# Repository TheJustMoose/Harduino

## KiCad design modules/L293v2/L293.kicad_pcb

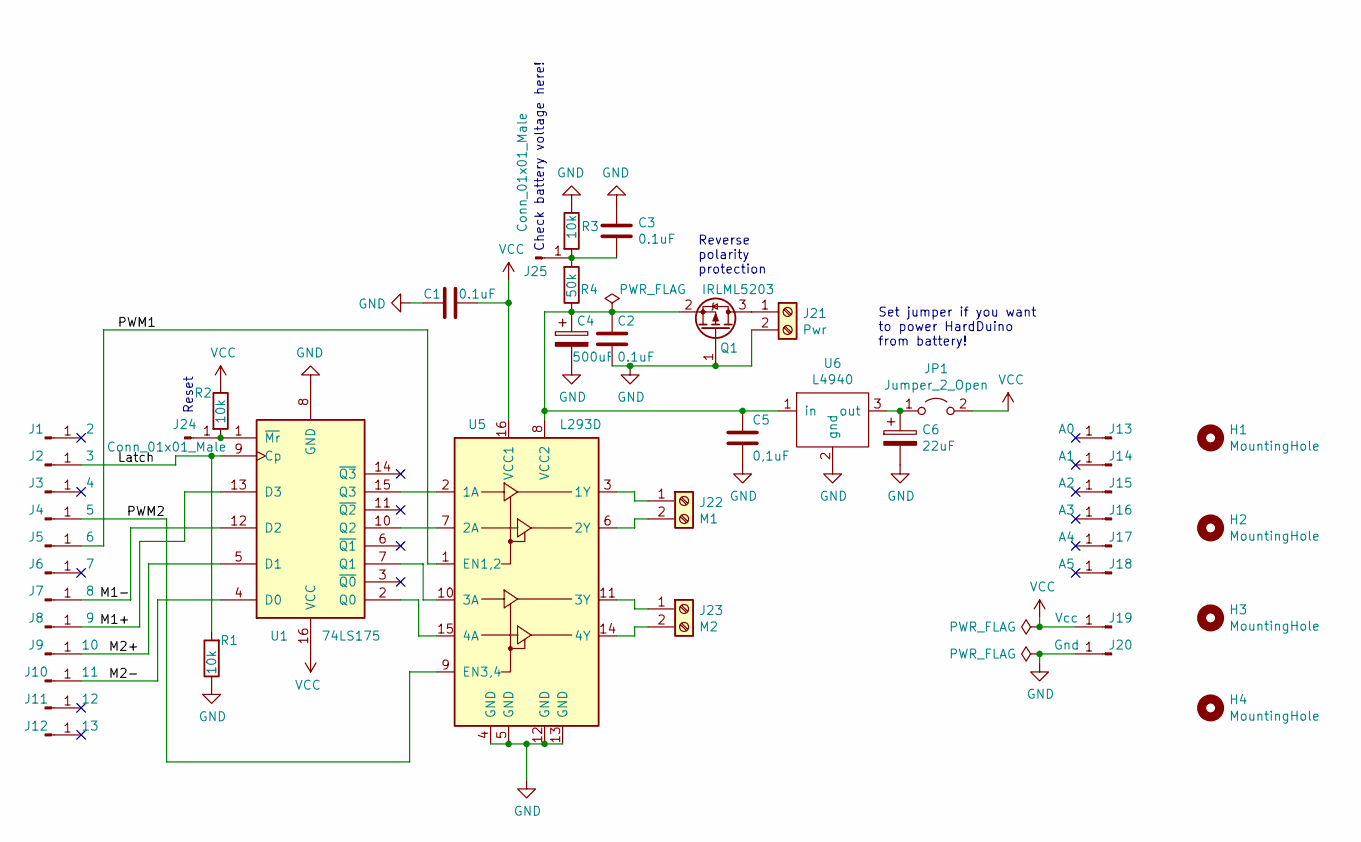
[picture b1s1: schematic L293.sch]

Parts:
C1, C2, C3: 0.1uF; C_0805_2012Metric_Pad1.15x1.40mm_HandSolder
C4: 500uF; CP_Radial_D8.0mm_P3.50mm
C5: 0,1uF; C_0805_2012Metric_Pad1.15x1.40mm_HandSolder
C6: 22uF; CP_Radial_D5.0mm_P2.50mm
H1, H2, H3, H4: MountingHole; MountingHole_3.2mm_M3
J1: 2; PinHeader_1x01_P2.54mm_Vertical
J2: 3; PinHeader_1x01_P2.54mm_Vertical
J3: 4; PinHeader_1x01_P2.54mm_Vertical
J4: 5; PinHeader_1x01_P2.54mm_Vertical
J5: 6; PinHeader_1x01_P2.54mm_Vertical
J6: 7; PinHeader_1x01_P2.54mm_Vertical
J7: 8; PinHeader_1x01_P2.54mm_Vertical
J8: 9; PinHeader_1x01_P2.54mm_Vertical
J9: 10; PinHeader_1x01_P2.54mm_Vertical
J10: 11; PinHeader_1x01_P2.54mm_Vertical
J11: 12; PinHeader_1x01_P2.54mm_Vertical
J12: 13; PinHeader_1x01_P2.54mm_Vertical
J13: A0; PinHeader_1x01_P2.54mm_Vertical
J14: A1; PinHeader_1x01_P2.54mm_Vertical
J15: A2; PinHeader_1x01_P2.54mm_Vertical
J16: A3; PinHeader_1x01_P2.54mm_Vertical
J17: A4; PinHeader_1x01_P2.54mm_Vertical
J18: A5; PinHeader_1x01_P2.54mm_Vertical
J19: Vcc; PinHeader_1x01_P2.54mm_Vertical
J20: Gnd; PinHeader_1x01_P2.54mm_Vertical
J21: Pwr; TerminalBlock_bornier-2_P5.08mm
J22: M1; TerminalBlock_bornier-2_P5.08mm
J23: M2; TerminalBlock_bornier-2_P5.08mm
J24, J25: Conn_01x01_Male; PinHeader_1x01_P2.54mm_Vertical
JP1: Jumper_2_Open; PinHeader_1x02_P2.54mm_Vertical
Q1: IRLML5203; SOT-23
R1, R2, R3: 10k; R_0805_2012Metric_Pad1.15x1.40mm_HandSolder
R4: 50k; R_0805_2012Metric_Pad1.15x1.40mm_HandSolder
U1: 74LS175; SOIC-16_3.9x9.9mm_P1.27mm
U5: L293D; DIP-16_W7.62mm
U6: L4940; TO-220-3_Horizontal_TabDown

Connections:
/Latch: J2.1, R1.2, U1.9 (Cp)
/M1+: J8.1, U1.13 (D3)
/M1-: J7.1, U1.12 (D2)
/M2+: J9.1, U1.5 (D1)
/M2-: J10.1, U1.4 (D0)
/PWM1: J5.1, U5.1 (EN1,2)
/PWM2: J4.1, U5.9 (EN3,4)
GND: C1.2, C2.1, C3.1, C4.2, C5.2, C6.2, J20.1, J21.2, Q1.1 (G), R1.1, R3.1, U1.8 (GND), U5.4 (GND), U5.5 (GND), U5.12 (GND), U5.13 (GND), U6.2 (gnd)
unnamed: C2.2, C4.1, C5.1, Q1.2 (S), R4.1, U5.8 (VCC2), U6.1 (in)
unnamed: C3.2, J25.1, R3.2, R4.2
unnamed: C6.1, JP1.1 (A), U6.3 (out)
unnamed: J21.1, Q1.3 (D)
unnamed: J22.1, U5.3 (1Y)
unnamed: J22.2, U5.6 (2Y)
unnamed: J23.1, U5.11 (3Y)
unnamed: J23.2, U5.14 (4Y)
unnamed: J24.1, R2.2, U1.1 (~Mr)
unnamed: U1.2 (Q0), U5.15 (4A)
unnamed: U1.7 (Q1), U5.10 (3A)
unnamed: U1.10 (Q2), U5.7 (2A)
unnamed: U1.15 (Q3), U5.2 (1A)
VCC: C1.1, J19.1, JP1.2 (B), R2.1, U1.16 (VCC), U5.16 (VCC1)

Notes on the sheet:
Set jumper if you want to power HardDuino from battery!
Check battery voltage here!
Reset
Reverse polarity protection

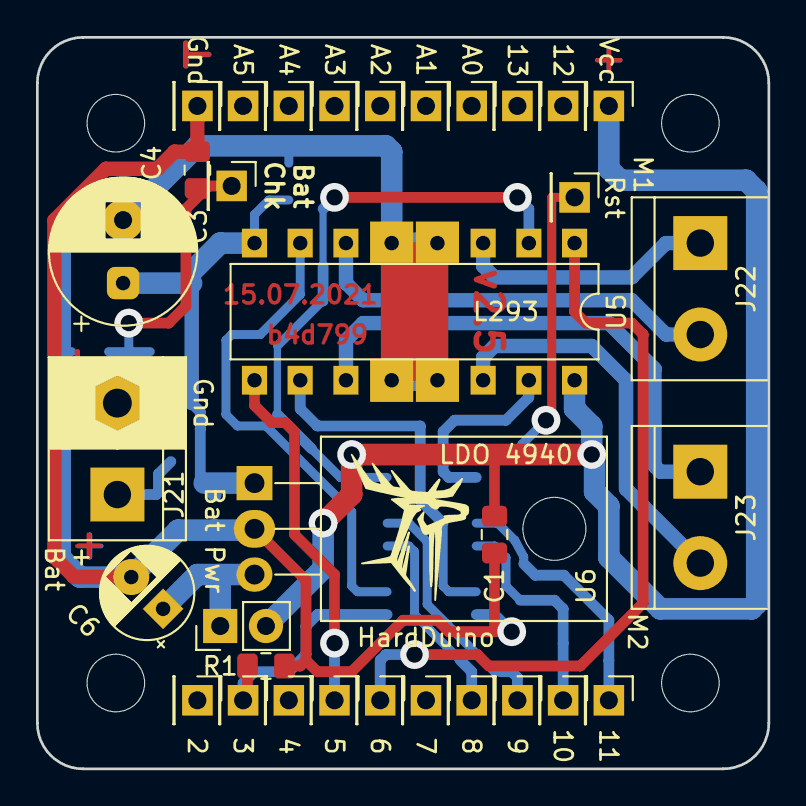
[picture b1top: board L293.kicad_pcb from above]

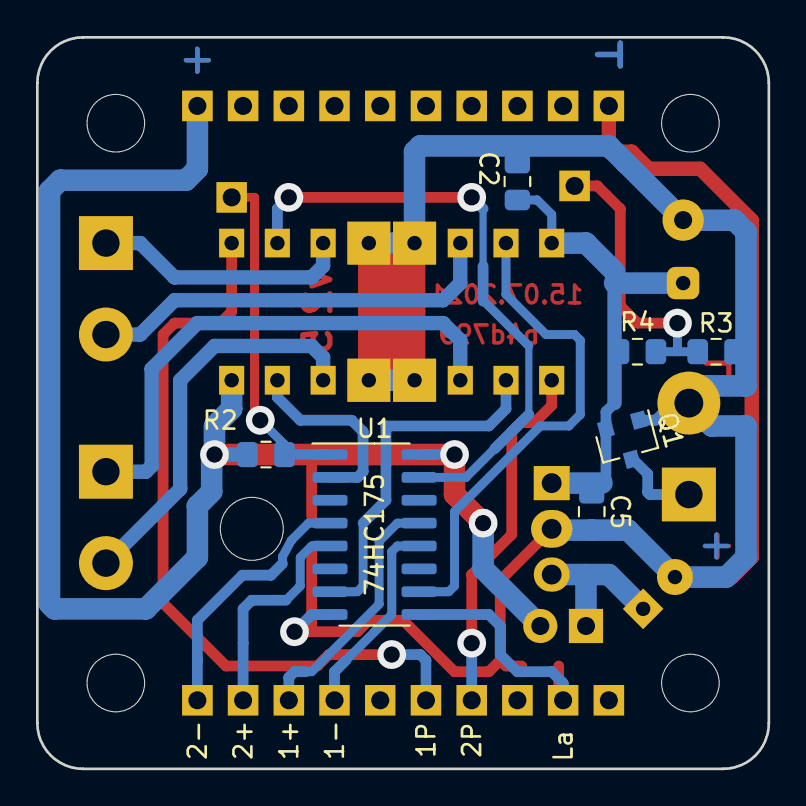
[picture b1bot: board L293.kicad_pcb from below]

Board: 2 copper layers, 40.6 x 40.6 mm, 44 parts (7 on the bottom side), 22 nets.

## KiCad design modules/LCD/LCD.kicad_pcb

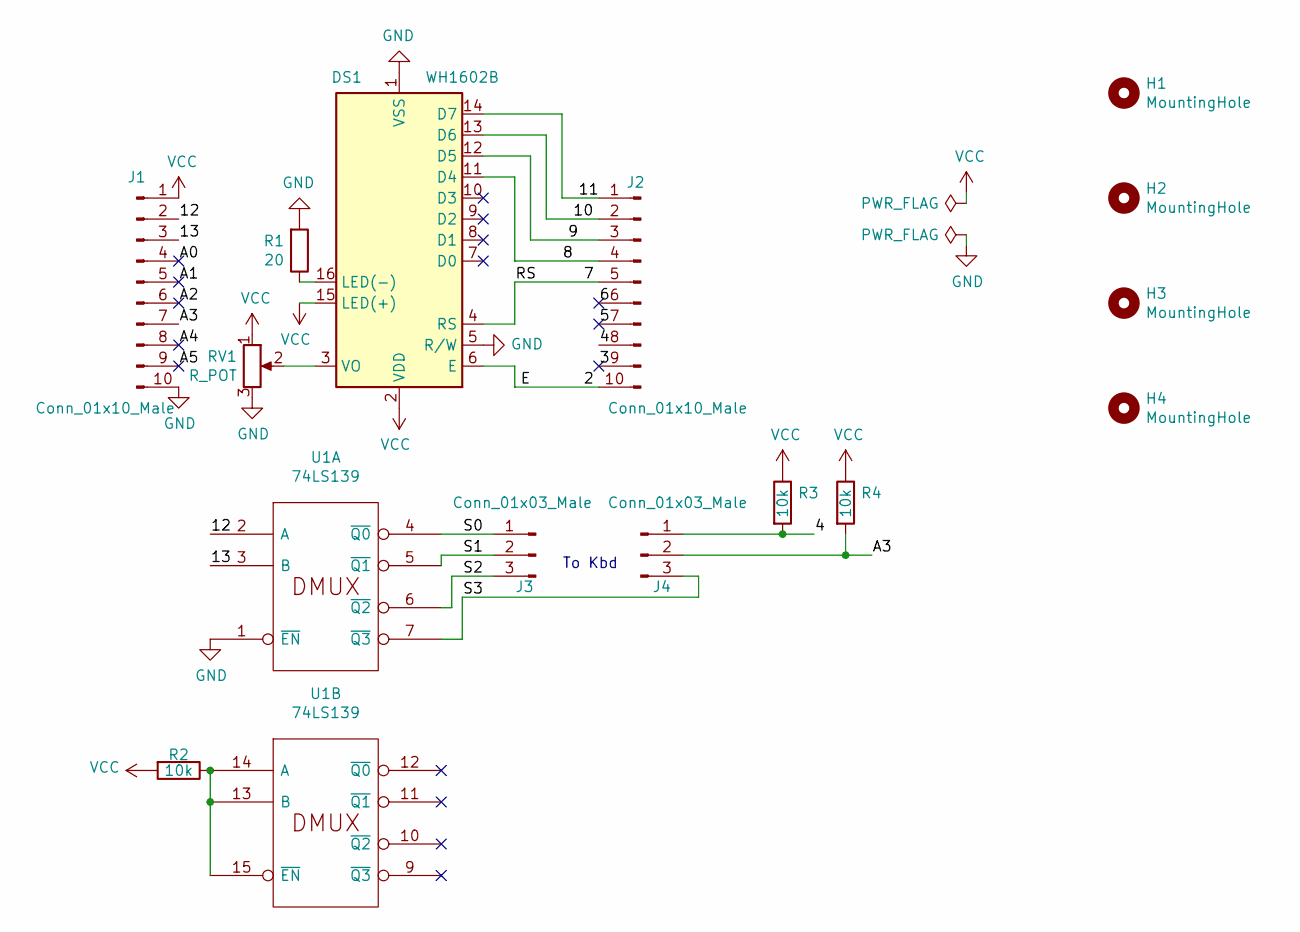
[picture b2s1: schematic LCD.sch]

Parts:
DS1: WH1602B; WH1602-2-holes
H1, H2, H3, H4: MountingHole; MountingHole_3.2mm_M3
J1, J2: Conn_01x10_Male; PinHeader_1x10_P2.54mm_Vertical
J3, J4: Conn_01x03_Male; PinHeader_1x03_P2.54mm_Horizontal
R1: 20; R_0805_2012Metric_Pad1.20x1.40mm_HandSolder
R2, R3, R4: 10k; R_0805_2012Metric_Pad1.20x1.40mm_HandSolder
RV1: R_POT; pot-5x5
U1: 74LS139; SOIC-16_3.9x9.9mm_P1.27mm

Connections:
/2: DS1.6 (E), J2.10
/3: J2.9
/4: J2.8, J4.1, R3.2
/5: J2.7
/6: J2.6
/7: DS1.4 (RS), J2.5
/8: DS1.11 (D4), J2.4
/9: DS1.12 (D5), J2.3
/10: DS1.13 (D6), J2.2
/11: DS1.14 (D7), J2.1
/12: J1.2, U1.2 (A)
/13: J1.3, U1.3 (B)
/A0: J1.4
/A1: J1.5
/A2: J1.6
/A3: J1.7, J4.2, R4.2
/A4: J1.8
/A5: J1.9
/S0: J3.1, U1.4 (~Q0)
/S1: J3.2, U1.5 (~Q1)
/S2: J3.3, U1.6 (~Q2)
/S3: J4.3, U1.7 (~Q3)
GND: DS1.1 (VSS), DS1.5 (R/W), J1.10, R1.2, RV1.3, U1.1 (~EN), U1.8 (GND)
unnamed: DS1.3 (VO), RV1.2
unnamed: DS1.16 (LED(-)), R1.1
unnamed: R2.1, U1.13 (B), U1.14 (A), U1.15 (~EN)
VCC: DS1.2 (VDD), DS1.15 (LED(+)), J1.1, R2.2, R3.1, R4.1, RV1.1, U1.16 (VCC)

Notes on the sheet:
To Kbd

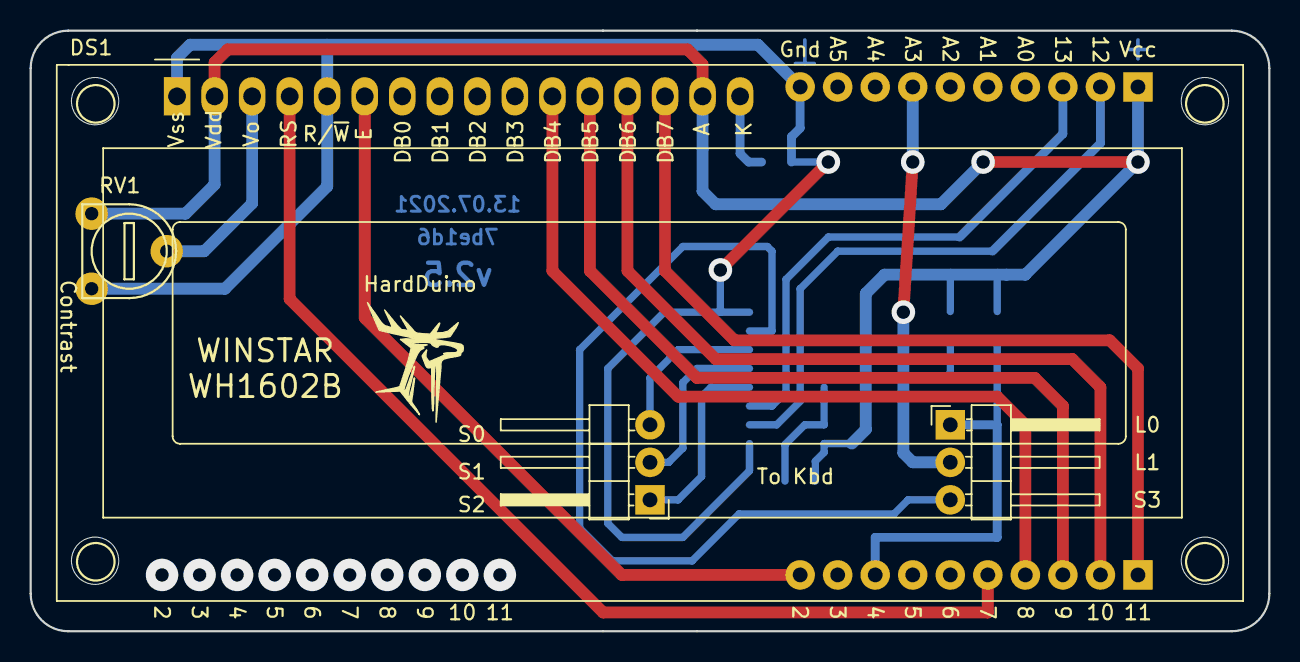
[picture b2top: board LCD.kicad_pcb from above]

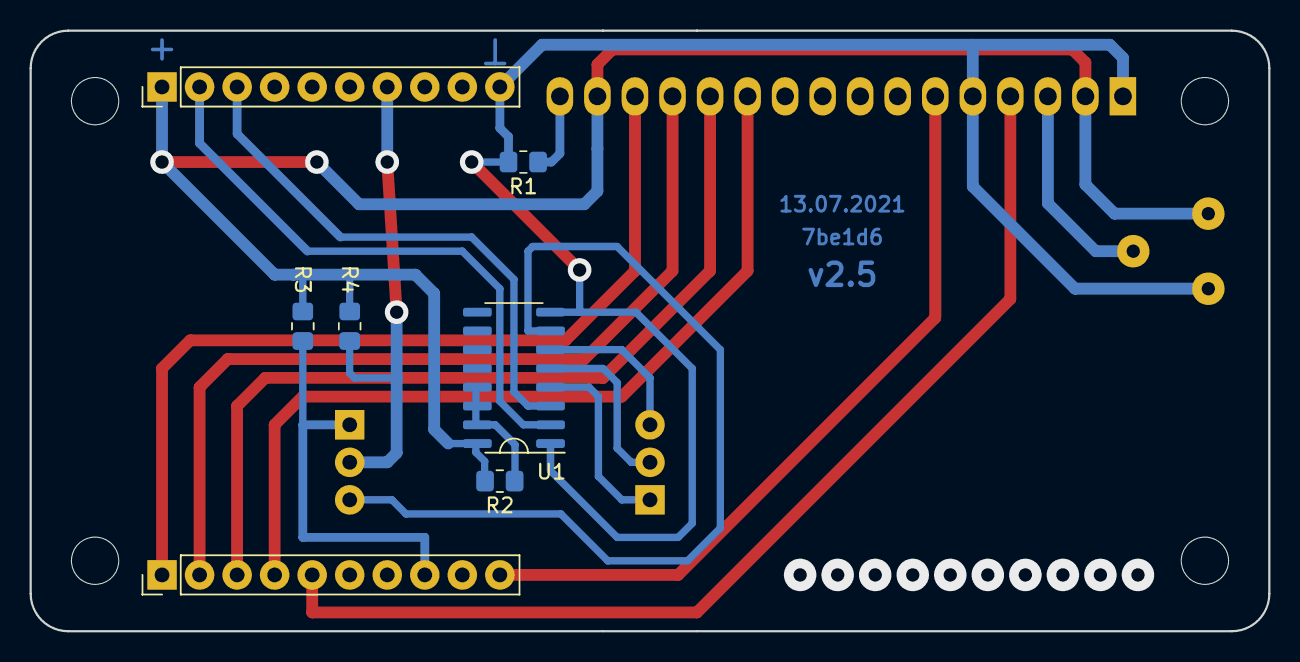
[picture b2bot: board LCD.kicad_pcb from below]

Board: 2 copper layers, 83.8 x 40.6 mm, 15 parts (7 on the bottom side), 19 nets.

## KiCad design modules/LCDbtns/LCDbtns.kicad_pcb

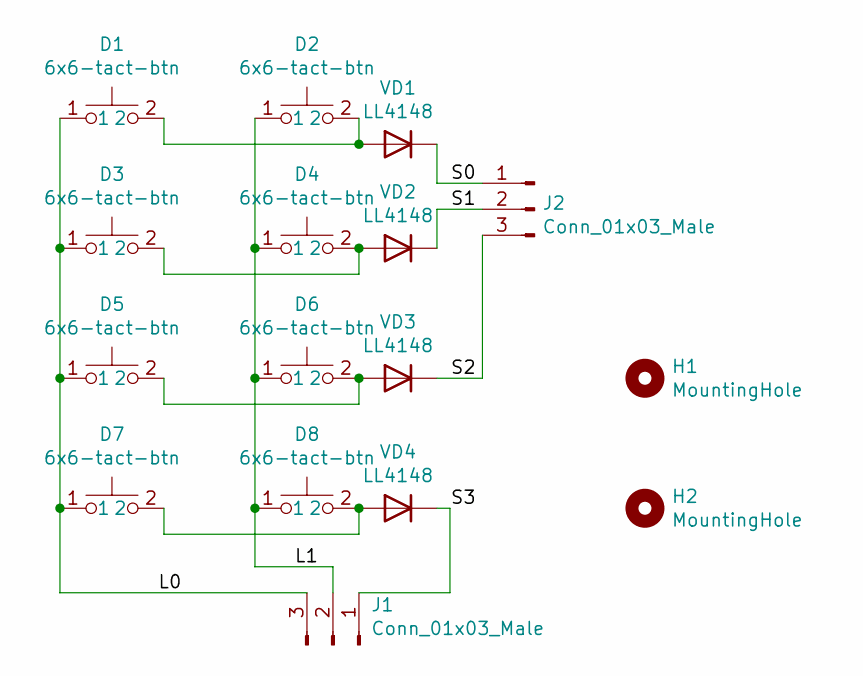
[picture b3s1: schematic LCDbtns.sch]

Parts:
D1, D2, D3, D4, D5, D6, D7, D8: 6x6-tact-btn
H1, H2: MountingHole; MountingHole_3.2mm_M3
J1, J2: Conn_01x03_Male; PinHeader_1x03_P2.54mm_Vertical
VD1, VD2, VD3, VD4: LL4148; D_MiniMELF

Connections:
/L0: D1.1, D3.1, D5.1, D7.1, J1.3
/L1: D2.1, D4.1, D6.1, D8.1, J1.2
/S0: J2.1, VD1.1 (K)
/S1: J2.2, VD2.1 (K)
/S2: J2.3, VD3.1 (K)
/S3: J1.1, VD4.1 (K)
unnamed: D1.2, D2.2, VD1.2 (A)
unnamed: D3.2, D4.2, VD2.2 (A)
unnamed: D5.2, D6.2, VD3.2 (A)
unnamed: D7.2, D8.2, VD4.2 (A)

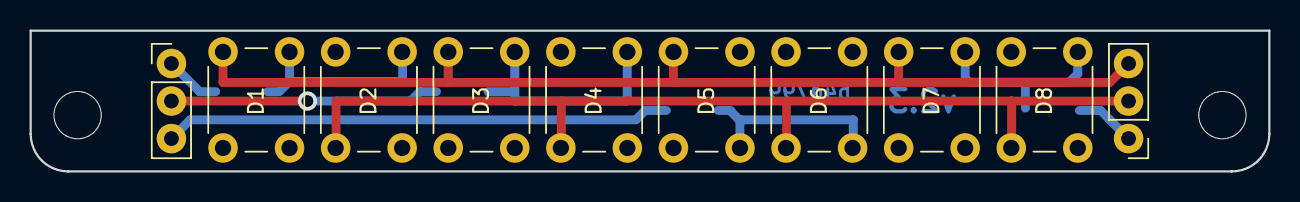
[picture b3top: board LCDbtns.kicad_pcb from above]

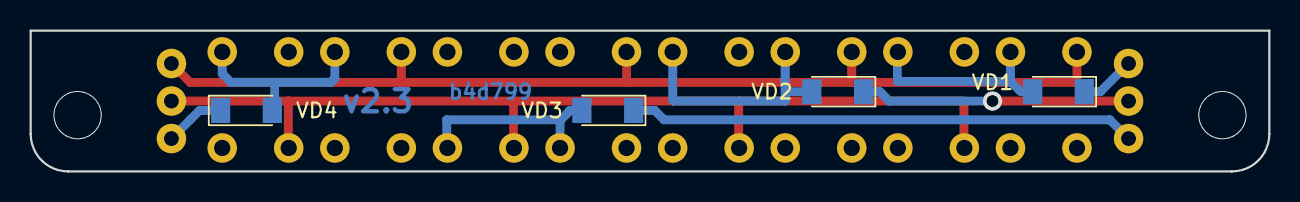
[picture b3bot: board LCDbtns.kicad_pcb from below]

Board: 2 copper layers, 83.8 x 9.5 mm, 16 parts (4 on the bottom side), 10 nets.

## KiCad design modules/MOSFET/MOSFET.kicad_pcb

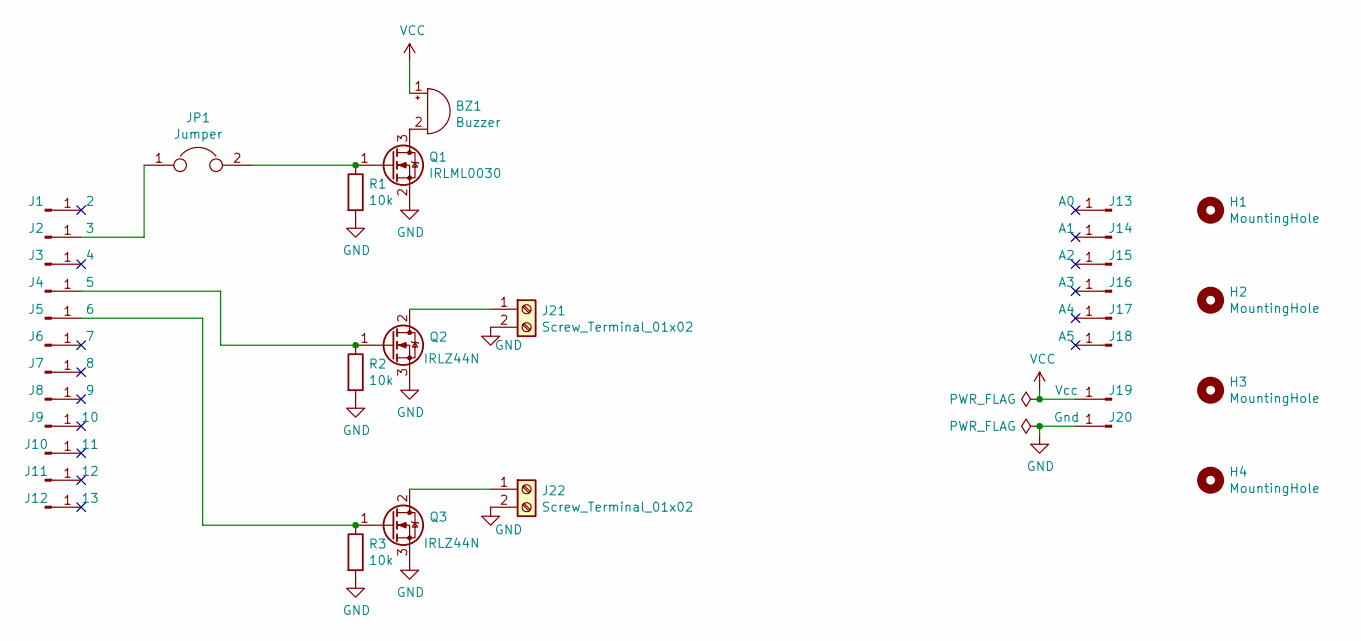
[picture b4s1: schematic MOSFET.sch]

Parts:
BZ1: Buzzer; Buzzer_12x9.5RM7.6
H1, H2, H3, H4: MountingHole; MountingHole_3.2mm_M3
J1: 2; PinHeader_1x01_P2.54mm_Vertical
J2: 3; PinHeader_1x01_P2.54mm_Vertical
J3: 4; PinHeader_1x01_P2.54mm_Vertical
J4: 5; PinHeader_1x01_P2.54mm_Vertical
J5: 6; PinHeader_1x01_P2.54mm_Vertical
J6: 7; PinHeader_1x01_P2.54mm_Vertical
J7: 8; PinHeader_1x01_P2.54mm_Vertical
J8: 9; PinHeader_1x01_P2.54mm_Vertical
J9: 10; PinHeader_1x01_P2.54mm_Vertical
J10: 11; PinHeader_1x01_P2.54mm_Vertical
J11: 12; PinHeader_1x01_P2.54mm_Vertical
J12: 13; PinHeader_1x01_P2.54mm_Vertical
J13: A0; PinHeader_1x01_P2.54mm_Vertical
J14: A1; PinHeader_1x01_P2.54mm_Vertical
J15: A2; PinHeader_1x01_P2.54mm_Vertical
J16: A3; PinHeader_1x01_P2.54mm_Vertical
J17: A4; PinHeader_1x01_P2.54mm_Vertical
J18: A5; PinHeader_1x01_P2.54mm_Vertical
J19: Vcc; PinHeader_1x01_P2.54mm_Vertical
J20: Gnd; PinHeader_1x01_P2.54mm_Vertical
J21, J22: Screw_Terminal_01x02; TerminalBlock_bornier-2_P5.08mm
JP1: Jumper; PinHeader_1x02_P2.54mm_Vertical
Q1: IRLML0030; SOT-23
Q2, Q3: IRLZ44N; TO-220-3_Horizontal_TabDown
R1, R2, R3: 10k; R_0805_2012Metric_Pad1.15x1.40mm_HandSolder

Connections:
GND: J20.1, J21.2, J22.2, Q1.2 (S), Q2.3 (S), Q3.3 (S), R1.2, R2.2, R3.2
unnamed: BZ1.2 (+), Q1.3 (D)
unnamed: J2.1, JP1.1
unnamed: J4.1, Q2.1 (G), R2.1
unnamed: J5.1, Q3.1 (G), R3.1
unnamed: J21.1, Q2.2 (D)
unnamed: J22.1, Q3.2 (D)
unnamed: JP1.2, Q1.1 (G), R1.1
VCC: BZ1.1 (-), J19.1

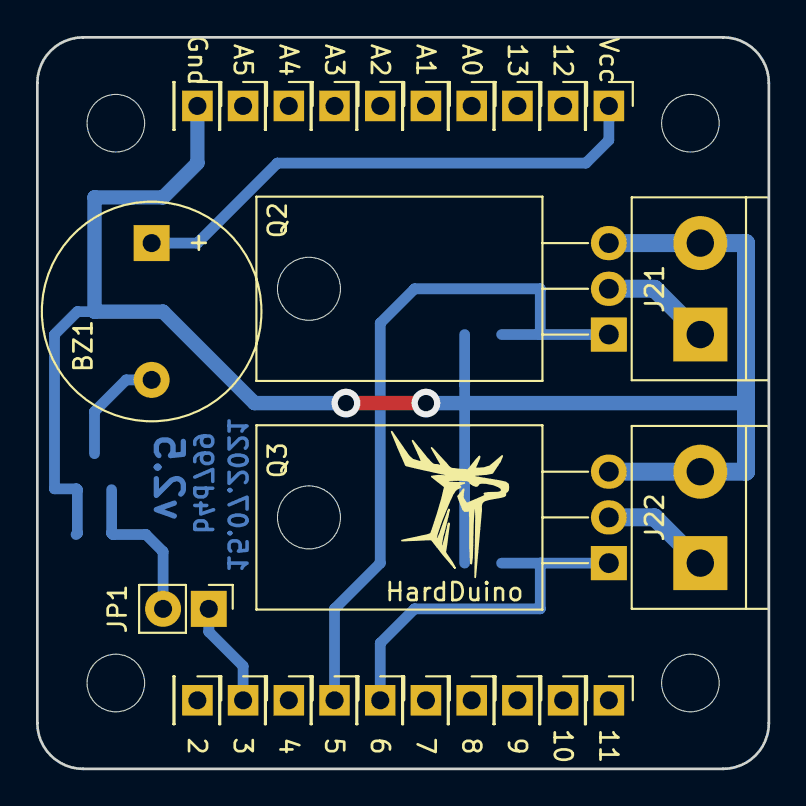
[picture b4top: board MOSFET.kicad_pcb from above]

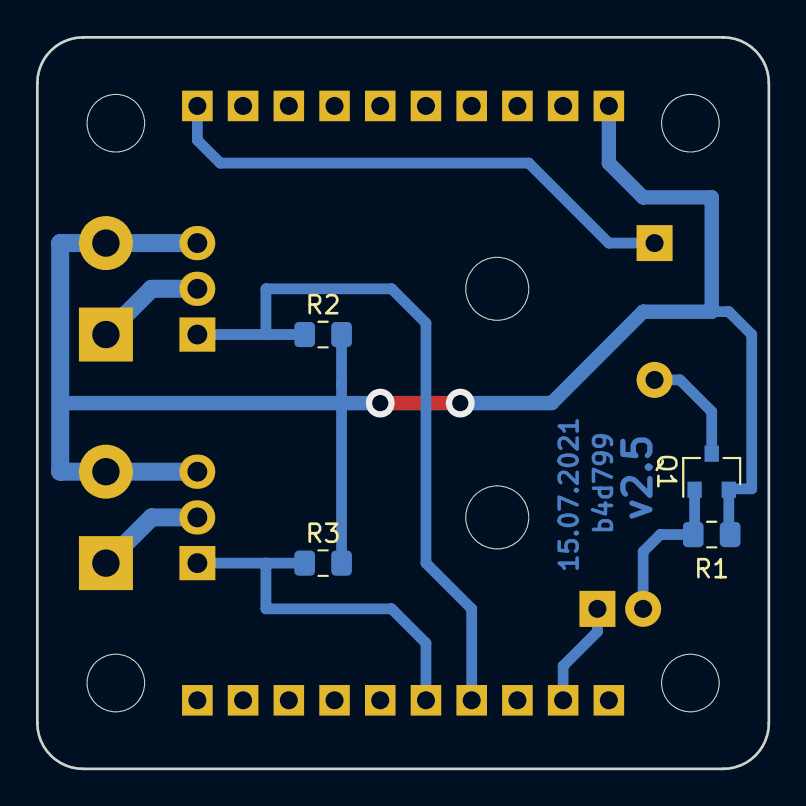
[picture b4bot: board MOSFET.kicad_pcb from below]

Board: 2 copper layers, 40.6 x 40.6 mm, 34 parts (4 on the bottom side), 9 nets.

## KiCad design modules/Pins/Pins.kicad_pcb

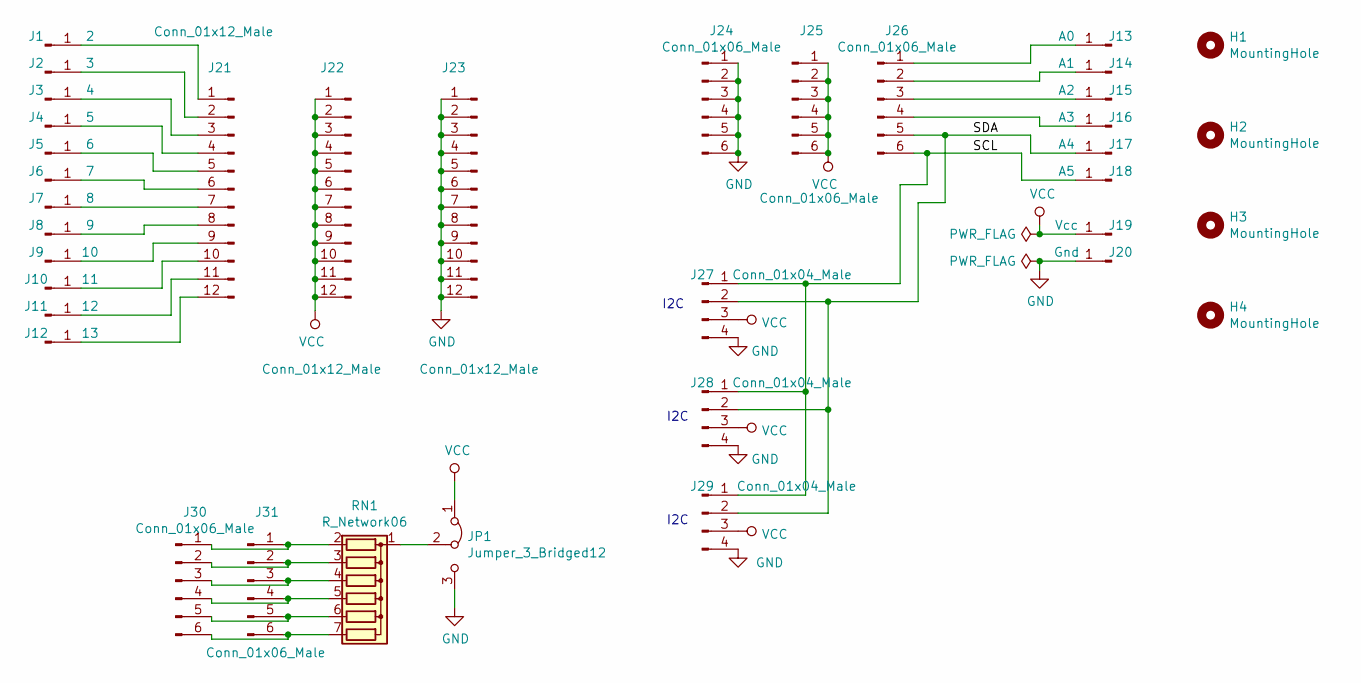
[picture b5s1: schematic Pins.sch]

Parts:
H1, H2, H3, H4: MountingHole; MountingHole_3.2mm_M3
J1: 2; PinHeader_1x01_P2.54mm_Vertical
J2: 3; PinHeader_1x01_P2.54mm_Vertical
J3: 4; PinHeader_1x01_P2.54mm_Vertical
J4: 5; PinHeader_1x01_P2.54mm_Vertical
J5: 6; PinHeader_1x01_P2.54mm_Vertical
J6: 7; PinHeader_1x01_P2.54mm_Vertical
J7: 8; PinHeader_1x01_P2.54mm_Vertical
J8: 9; PinHeader_1x01_P2.54mm_Vertical
J9: 10; PinHeader_1x01_P2.54mm_Vertical
J10: 11; PinHeader_1x01_P2.54mm_Vertical
J11: 12; PinHeader_1x01_P2.54mm_Vertical
J12: 13; PinHeader_1x01_P2.54mm_Vertical
J13: A0; PinHeader_1x01_P2.54mm_Vertical
J14: A1; PinHeader_1x01_P2.54mm_Vertical
J15: A2; PinHeader_1x01_P2.54mm_Vertical
J16: A3; PinHeader_1x01_P2.54mm_Vertical
J17: A4; PinHeader_1x01_P2.54mm_Vertical
J18: A5; PinHeader_1x01_P2.54mm_Vertical
J19: Vcc; PinHeader_1x01_P2.54mm_Vertical
J20: Gnd; PinHeader_1x01_P2.54mm_Vertical
J21, J22, J23: Conn_01x12_Male; PinHeader_1x12_P2.54mm_Vertical
J24, J25, J26, J30, J31: Conn_01x06_Male; PinHeader_1x06_P2.54mm_Vertical
J27, J28, J29: Conn_01x04_Male; PinHeader_1x04_P2.54mm_Vertical
JP1: Jumper_3_Bridged12; PinHeader_1x03_P2.54mm_Vertical
RN1: R_Network06; R_Array_SIP7

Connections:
/SCL: J18.1, J26.6, J27.1, J28.1, J29.1
/SDA: J17.1, J26.5, J27.2, J28.2, J29.2
GND: J20.1, J23.1, J23.2, J23.3, J23.4, J23.5, J23.6, J23.7, J23.8, J23.9, J23.10, J23.11, J23.12, J24.1, J24.2, J24.3, J24.4, J24.5, J24.6, J27.4, J28.4, J29.4, JP1.3 (B)
unnamed: J1.1, J21.1
unnamed: J2.1, J21.2
unnamed: J10.1, J21.10
unnamed: J11.1, J21.11
unnamed: J12.1, J21.12
unnamed: J13.1, J26.1
unnamed: J14.1, J26.2
unnamed: J15.1, J26.3
unnamed: J16.1, J26.4
unnamed: J3.1, J21.3
unnamed: J4.1, J21.4
unnamed: J5.1, J21.5
unnamed: J6.1, J21.6
unnamed: J7.1, J21.7
unnamed: J8.1, J21.8
unnamed: J9.1, J21.9
unnamed: J30.1, J31.1, RN1.2 (R1)
unnamed: J30.2, J31.2, RN1.3 (R2)
unnamed: J30.3, J31.3, RN1.4 (R3)
unnamed: J30.4, J31.4, RN1.5 (R4)
unnamed: J30.5, J31.5, RN1.6 (R5)
unnamed: J30.6, J31.6, RN1.7 (R6)
unnamed: JP1.2 (C), RN1.1 (common)
VCC: J19.1, J22.1, J22.2, J22.3, J22.4, J22.5, J22.6, J22.7, J22.8, J22.9, J22.10, J22.11, J22.12, J25.1, J25.2, J25.3, J25.4, J25.5, J25.6, J27.3, J28.3, J29.3, JP1.1 (A)

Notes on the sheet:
I2C

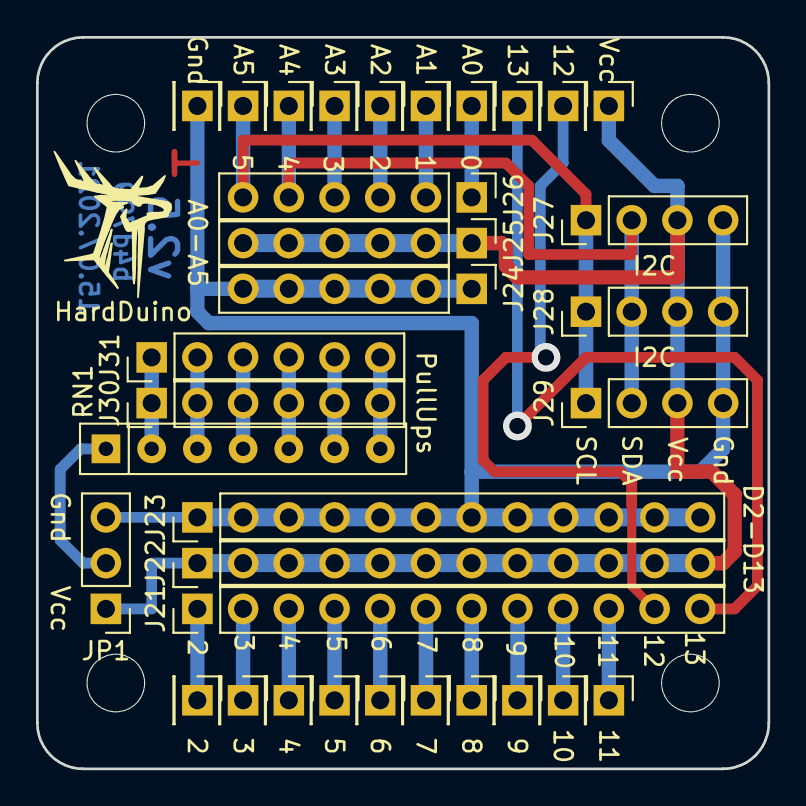
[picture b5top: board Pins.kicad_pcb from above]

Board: 2 copper layers, 40.6 x 40.6 mm, 37 parts (0 on the bottom side), 27 nets.

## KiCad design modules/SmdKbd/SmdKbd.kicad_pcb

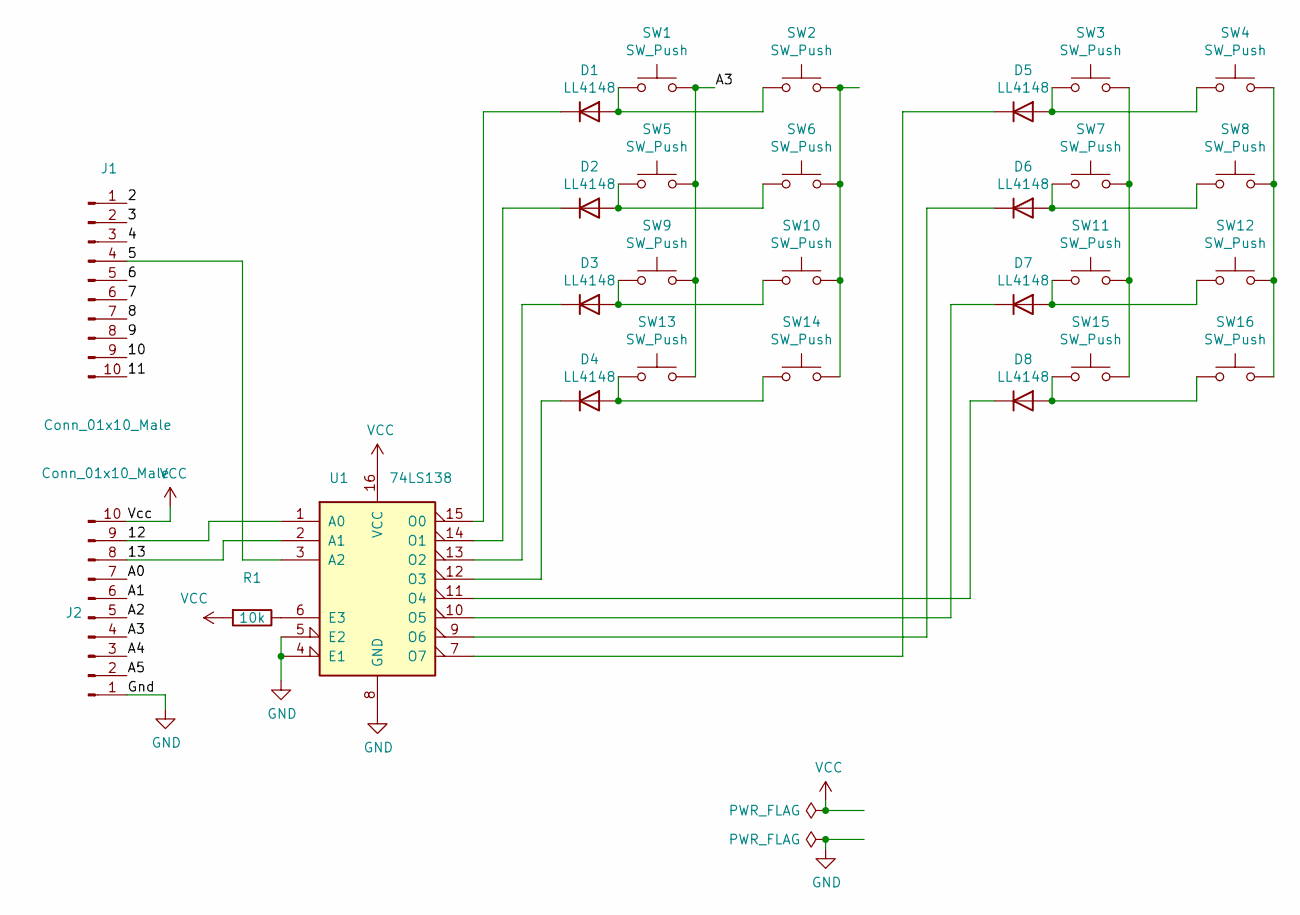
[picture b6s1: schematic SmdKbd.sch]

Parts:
D1, D2, D3, D4, D5, D6, D7, D8: LL4148; D_MiniMELF
J1, J2: Conn_01x10_Male; PinHeader_1x10_P2.54mm_Vertical_SMD_Pin1Left
R1: 10k; R_0805_2012Metric_Pad1.15x1.40mm_HandSolder
SW1, SW2, SW3, SW4, SW5, SW6, SW7, SW8, SW9, SW10, SW11, SW12, SW13, SW14, SW15, SW16: SW_Push; SW_Push_1P1T_NO_6x6mm_H9.5mm
U1: 74LS138; SOIC-16_3.9x9.9mm_P1.27mm

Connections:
/2: J1.1
/3: J1.2
/4: J1.3
/5: J1.4, U1.3 (A2)
/6: J1.5
/7: J1.6
/8: J1.7
/9: J1.8
/10: J1.9
/11: J1.10
/12: J2.9, U1.1 (A0)
/13: J2.8, U1.2 (A1)
/A0: J2.7
/A1: J2.6
/A2: J2.5
/A3: J2.4, SW1.2, SW5.2, SW9.2, SW13.2
/A4: J2.3
/A5: J2.2
GND: J2.1, U1.4 (E1), U1.5 (E2), U1.8 (GND)
unnamed: D1.1 (K), U1.15 (O0)
unnamed: D1.2 (A), SW1.1, SW2.1
unnamed: D2.1 (K), U1.14 (O1)
unnamed: D2.2 (A), SW5.1, SW6.1
unnamed: D3.1 (K), U1.13 (O2)
unnamed: D3.2 (A), SW9.1, SW10.1
unnamed: D4.1 (K), U1.12 (O3)
unnamed: D4.2 (A), SW13.1, SW14.1
unnamed: D5.1 (K), U1.7 (O7)
unnamed: D5.2 (A), SW3.1, SW4.1
unnamed: D6.1 (K), U1.9 (O6)
unnamed: D6.2 (A), SW7.1, SW8.1
unnamed: D7.1 (K), U1.10 (O5)
unnamed: D7.2 (A), SW11.1, SW12.1
unnamed: D8.1 (K), U1.11 (O4)
unnamed: D8.2 (A), SW15.1, SW16.1
unnamed: R1.1, U1.6 (E3)
unnamed: SW2.2, SW6.2, SW10.2, SW14.2
unnamed: SW3.2, SW7.2, SW11.2, SW15.2
unnamed: SW4.2, SW8.2, SW12.2, SW16.2
VCC: J2.10, R1.2, U1.16 (VCC)

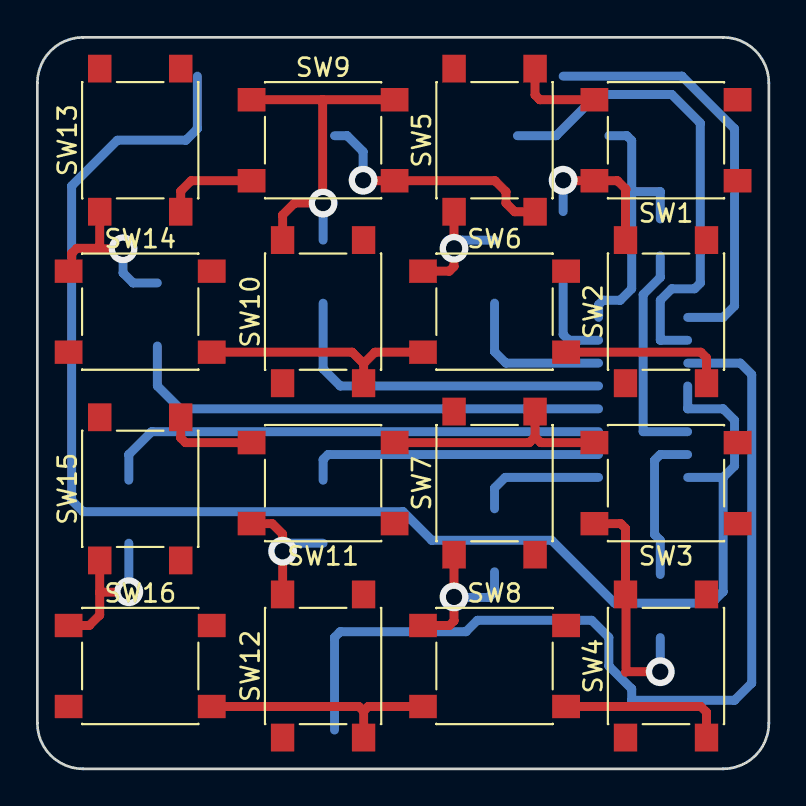
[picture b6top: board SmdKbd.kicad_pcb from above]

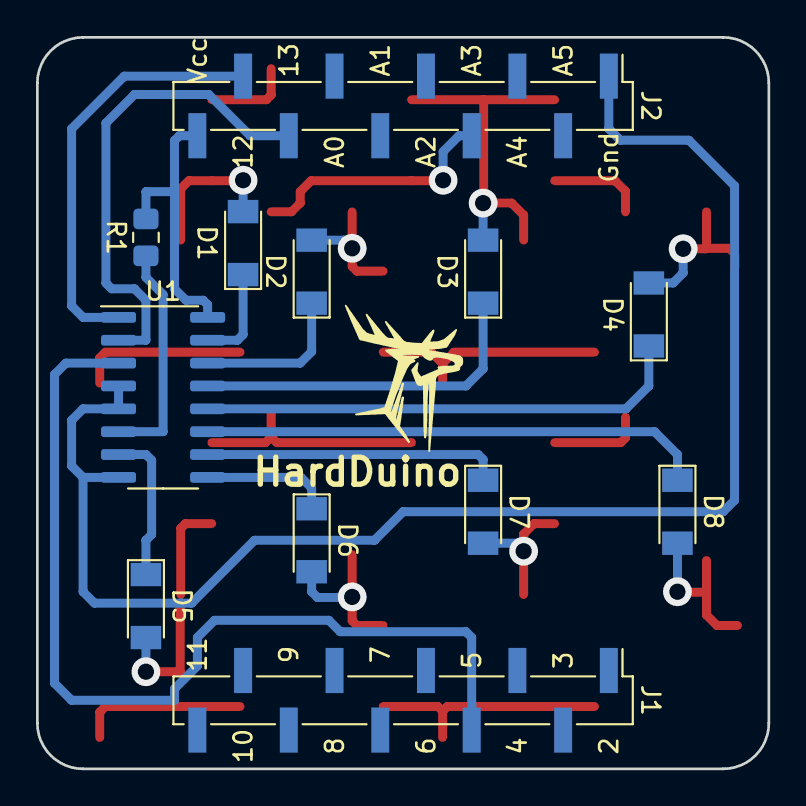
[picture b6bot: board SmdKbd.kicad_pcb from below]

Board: 2 copper layers, 40.6 x 40.6 mm, 28 parts (12 on the bottom side), 26 nets.

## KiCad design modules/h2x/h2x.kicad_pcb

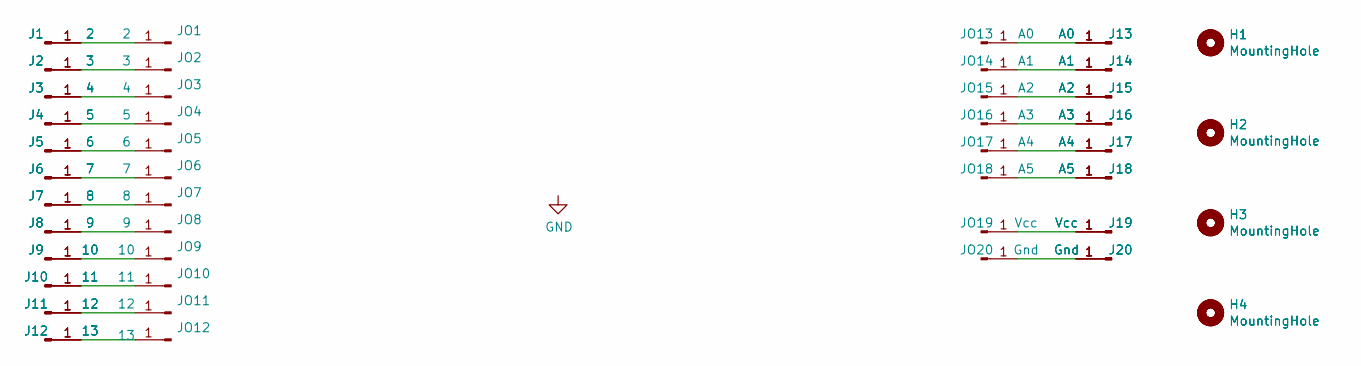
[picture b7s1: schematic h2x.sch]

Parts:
H1, H2, H3, H4: MountingHole; MountingHole_3.2mm_M3
J1: 2; PinHeader_1x01_P2.54mm_Vertical
J2: 3; PinHeader_1x01_P2.54mm_Vertical
J3: 4; PinHeader_1x01_P2.54mm_Vertical
J4: 5; PinHeader_1x01_P2.54mm_Vertical
J5: 6; PinHeader_1x01_P2.54mm_Vertical
J6: 7; PinHeader_1x01_P2.54mm_Vertical
J7: 8; PinHeader_1x01_P2.54mm_Vertical
J8: 9; PinHeader_1x01_P2.54mm_Vertical
J9: 10; PinHeader_1x01_P2.54mm_Vertical
J10: 11; PinHeader_1x01_P2.54mm_Vertical
J11: 12; PinHeader_1x01_P2.54mm_Vertical
J12: 13; PinHeader_1x01_P2.54mm_Vertical
J13: A0; PinHeader_1x01_P2.54mm_Vertical
J14: A1; PinHeader_1x01_P2.54mm_Vertical
J15: A2; PinHeader_1x01_P2.54mm_Vertical
J16: A3; PinHeader_1x01_P2.54mm_Vertical
J17: A4; PinHeader_1x01_P2.54mm_Vertical
J18: A5; PinHeader_1x01_P2.54mm_Vertical
J19: Vcc; PinHeader_1x01_P2.54mm_Vertical
J20: Gnd; PinHeader_1x01_P2.54mm_Vertical
JO1: 2; PinHeader_1x01_P2.54mm_Vertical
JO2: 3; PinHeader_1x01_P2.54mm_Vertical
JO3: 4; PinHeader_1x01_P2.54mm_Vertical
JO4: 5; PinHeader_1x01_P2.54mm_Vertical
JO5: 6; PinHeader_1x01_P2.54mm_Vertical
JO6: 7; PinHeader_1x01_P2.54mm_Vertical
JO7: 8; PinHeader_1x01_P2.54mm_Vertical
JO8: 9; PinHeader_1x01_P2.54mm_Vertical
JO9: 10; PinHeader_1x01_P2.54mm_Vertical
JO10: 11; PinHeader_1x01_P2.54mm_Vertical
JO11: 12; PinHeader_1x01_P2.54mm_Vertical
JO12: 13; PinHeader_1x01_P2.54mm_Vertical
JO13: A0; PinHeader_1x01_P2.54mm_Vertical
JO14: A1; PinHeader_1x01_P2.54mm_Vertical
JO15: A2; PinHeader_1x01_P2.54mm_Vertical
JO16: A3; PinHeader_1x01_P2.54mm_Vertical
JO17: A4; PinHeader_1x01_P2.54mm_Vertical
JO18: A5; PinHeader_1x01_P2.54mm_Vertical
JO19: Vcc; PinHeader_1x01_P2.54mm_Vertical
JO20: Gnd; PinHeader_1x01_P2.54mm_Vertical

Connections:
unnamed: J1.1, JO1.1
unnamed: J2.1, JO2.1
unnamed: J3.1, JO3.1
unnamed: J4.1, JO4.1
unnamed: J5.1, JO5.1
unnamed: J6.1, JO6.1
unnamed: J7.1, JO7.1
unnamed: J8.1, JO8.1
unnamed: J9.1, JO9.1
unnamed: J10.1, JO10.1
unnamed: J11.1, JO11.1
unnamed: J12.1, JO12.1
unnamed: J13.1, JO13.1
unnamed: J14.1, JO14.1
unnamed: J15.1, JO15.1
unnamed: J16.1, JO16.1
unnamed: J17.1, JO17.1
unnamed: J18.1, JO18.1
unnamed: J19.1, JO19.1
unnamed: J20.1, JO20.1

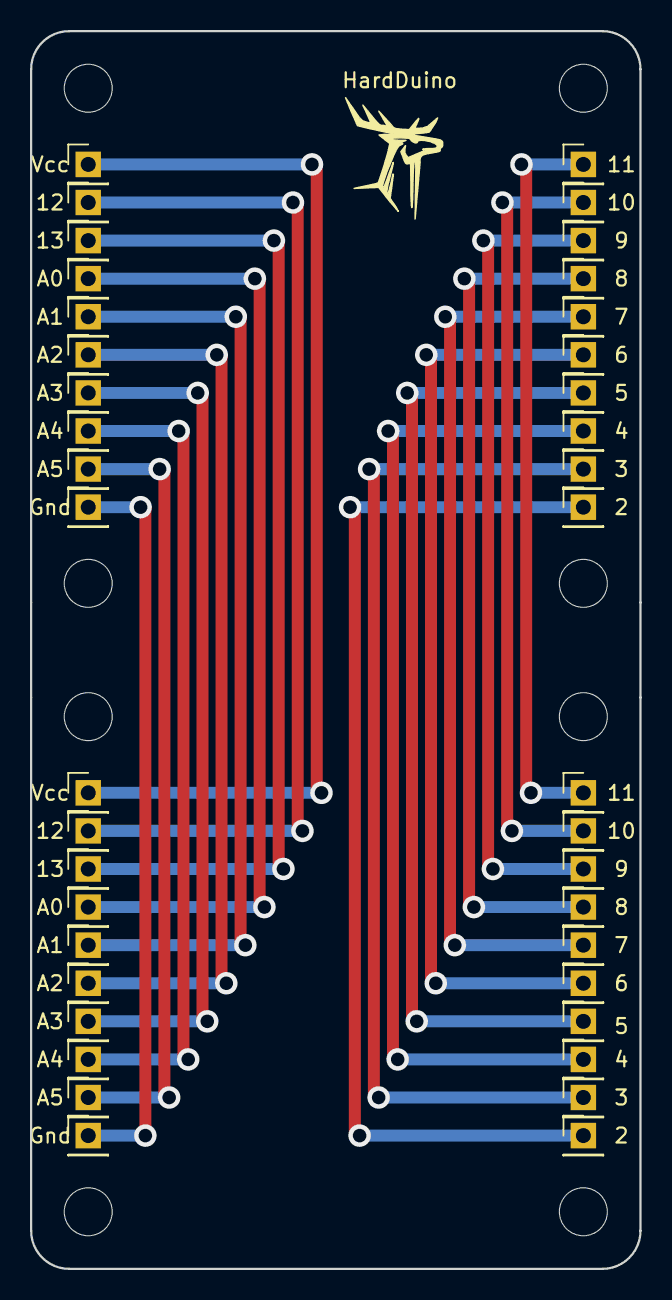
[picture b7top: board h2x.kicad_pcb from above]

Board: 2 copper layers, 40.6 x 82.5 mm, 48 parts (0 on the bottom side), 20 nets.

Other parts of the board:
H1#2, H2#2, H3#2, H4#2: MountingHole; MountingHole_3.2mm_M3
